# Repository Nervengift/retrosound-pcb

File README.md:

# What is this?

This is a PCB for the "Elektronik-Retro-Sound Adventskalender" by Franzis press.

The original kit is built on breadboard but I wanted a more durable solution taking less space and made a quick PCB design for it.

# Parts

All parts are included in the kit except for an optional power switch (SW5) and optional terminal blocks for speaker and battery. I would recommend to at least add pin headers and a jumper for SW5 when soldering the battery pack directly. Otherwise you can't turn the device off without removing the batteries from the holder.

When not using SW5, solder JP1 closed. This will bridge SW5 to be always closed.

| Reference | Value     | Notes                                             |
| --------- | --------- | ------------------------------------------------- |
| C1-C4     | 104       |                                                   |
| C5, C6    | 100uF     | white - mark facing left (direction of pots)      |
| D1-D8     | LED       | short leg facing left                             |
| R1, R5    | 1kΩ       |                                                   |
| R2        | 100kΩ     |                                                   |
| R3        | 560Ω      |                                                   |
| R4        | 15kΩ      |                                                   |
| RV1-RV3   | 10kΩ pot  |                                                   |
| SW1-SW4   | button    |                                                   |
| U1        | soundchip |                                                   |
| U2        | LM386     |                                                   |
| BT1       | battery   | solder directly or add screw terminal (5mm pitch) |
| LS1       | speaker   | solder directly or add screw terminal (5mm pitch) |
| SW5       |           | (optional, not included originally) add a 2.54mm pitch switch or jumper to switch the battery power on and off |
| JP1       |           | solder closed if not using SW5 to force it closed |

# License

[CC0](https://creativecommons.org/share-your-work/public-domain/cc0/), some rights might be reserved by Franzis for the original kit.

But please drop me a note if you do something fun with it :)

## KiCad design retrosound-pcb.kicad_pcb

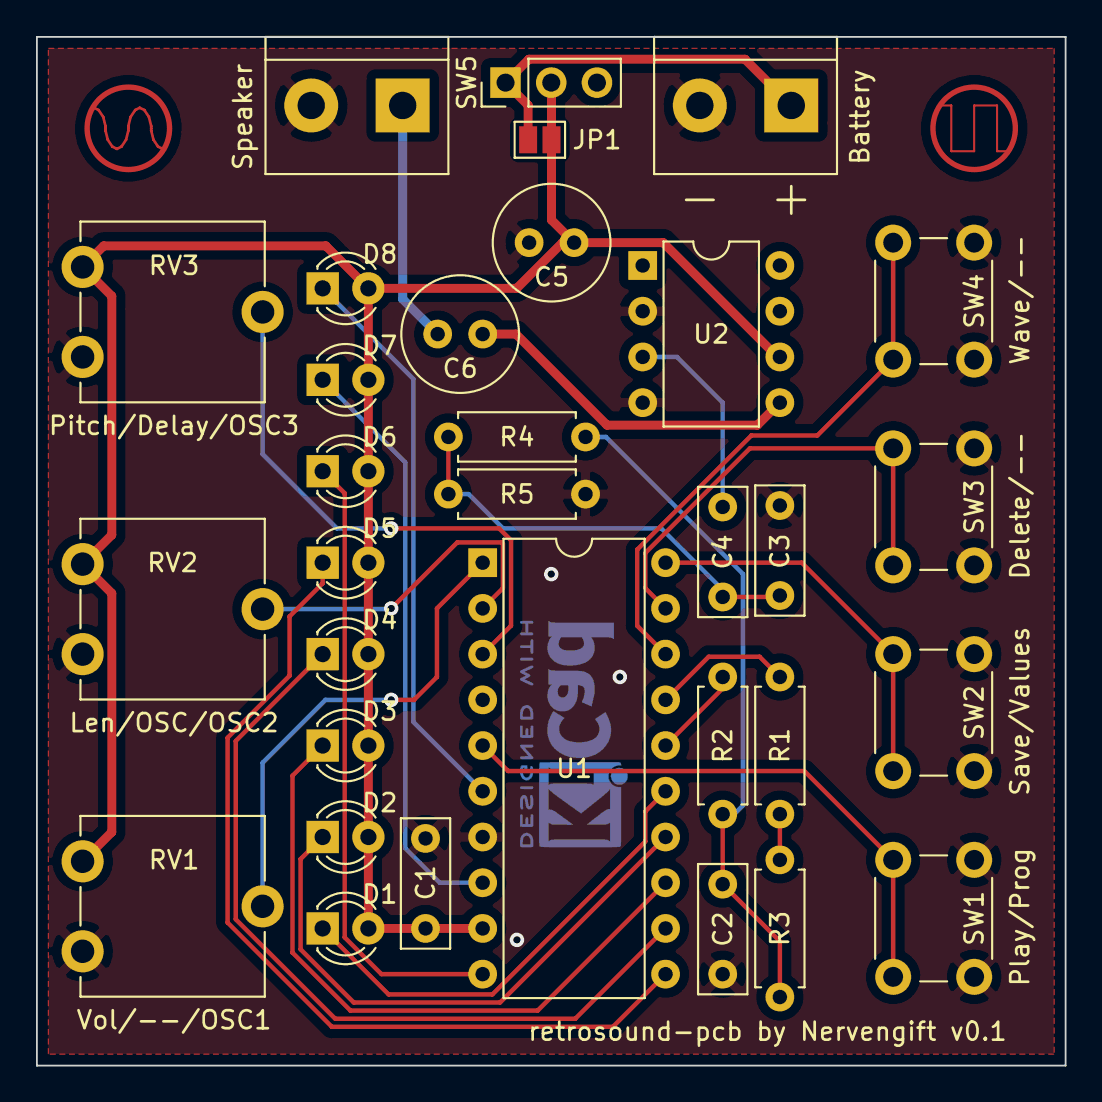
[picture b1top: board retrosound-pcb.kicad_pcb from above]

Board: 2 copper layers, 57.1 x 57.1 mm, 32 parts (0 on the bottom side), 26 nets.

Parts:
Battery: Battery_Cell; TerminalBlock_bornier-2_P5.08mm
C1, C2, C3, C4: 104; C_Disc_D7.0mm_W2.5mm_P5.00mm
C5, C6: 100uF; C_Radial_D6.3mm_H11.0mm_P2.50mm
D1, D2, D3, D4, D5, D6, D7, D8: LED; LED_D3.0mm
JP1: SolderJumper_2_Open; SolderJumper-2_P1.3mm_Open_Pad1.0x1.5mm
R1, R5: 1k; R_Axial_DIN0207_L6.3mm_D2.5mm_P7.62mm_Horizontal
R2: 100k; R_Axial_DIN0207_L6.3mm_D2.5mm_P7.62mm_Horizontal
R3: 560; R_Axial_DIN0207_L6.3mm_D2.5mm_P7.62mm_Horizontal
R4: 15k; R_Axial_DIN0207_L6.3mm_D2.5mm_P7.62mm_Horizontal
RV1, RV2, RV3: 10k; Potentiometer_ACP_CA9-V10_Vertical
SW1, SW2, SW3, SW4: SW_Push; SW_PUSH_6mm
SW5: SW_SPST; PinHeader_1x03_P2.54mm_Vertical
Speaker: Speaker; TerminalBlock_bornier-2_P5.08mm
U1: soundchip; DIP-20_W10.16mm
U2: LM386; DIP-8_W7.62mm

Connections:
GND: Battery.2, C1.2, C2.1, C3.1, C5.2, R5.2, RV1.1, RV2.1, RV3.1, SW1.1, SW2.1, SW3.1, SW4.1, Speaker.2, U1.7, U2.2, U2.4
unnamed: Battery.1, JP1.1, SW5.1
unnamed: C2.2, R2.2, R3.1, R4.1
unnamed: C3.2, C4.1, R4.2, R5.1
unnamed: C4.2, U2.3
unnamed: C6.1, U2.5
unnamed: C6.2, Speaker.1
unnamed: D1.1, U1.15
unnamed: D2.1, U1.14
unnamed: D3.1, U1.13
unnamed: D4.1, U1.12
unnamed: D5.1, U1.11
unnamed: D6.1, U1.10
unnamed: D7.1, U1.8
unnamed: D8.1, U1.6
unnamed: R1.1, U1.17
unnamed: R1.2, R3.2
unnamed: R2.1, U1.16
unnamed: RV1.2, U1.1
unnamed: RV2.2, U1.2
unnamed: RV3.2, U1.3
unnamed: SW1.2, U1.5
unnamed: SW2.2, U1.20
unnamed: SW3.2, U1.19
unnamed: SW4.2, U1.18
VCC: C1.1, C5.1, D1.2, D2.2, D3.2, D4.2, D5.2, D6.2, D7.2, D8.2, JP1.2, RV1.3, RV2.3, RV3.3, SW5.2, U1.9, U2.6

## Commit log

2022-03-21 Add license info
2022-03-21 more precise name of the kit
2022-03-21 copyright clarification
